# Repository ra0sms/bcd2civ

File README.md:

## Converter Yaesu BCD to Icom CI-V band data

A simple board is based on risk-v MCU CH32V003F4P6. 

* Dimensions: 70*45 mm
* Consumption current: 20 mA
* Power supply: from 7 to 20VDC
* CI-V address: 0x7A
* Baud rate for EW3MM tuner: 9600 kb/s
* Baud rate for DJ0ABR controller: 4800 kb/s

[Firmware for EU3MM tuner](code/obj/bcd2civ_tuner.hex)

[Firmware for DJ0ABR controller](code/obj/bcd2civ_dj0abr.hex)

More information - https://ra0sms.com/bcd2civ

### Yaesu BCD band data:

### Schematic:

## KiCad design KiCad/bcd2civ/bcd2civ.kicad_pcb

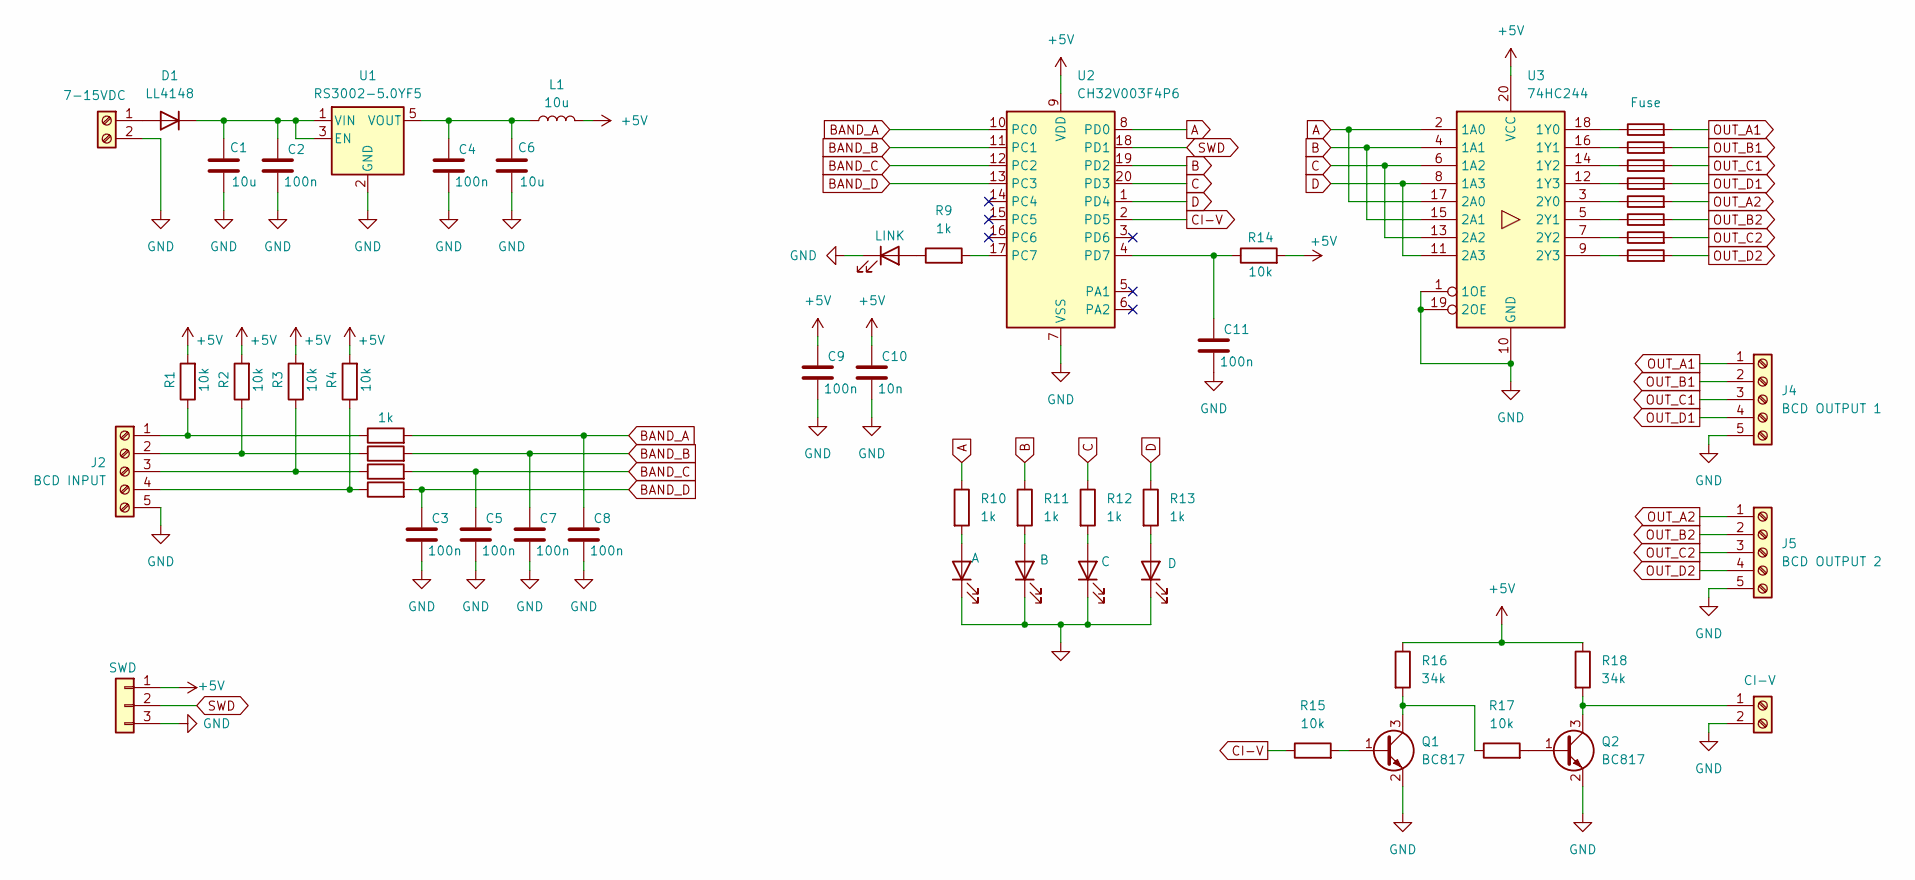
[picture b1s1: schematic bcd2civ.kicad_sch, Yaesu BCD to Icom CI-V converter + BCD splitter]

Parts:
C1, C6: 10u; C_1206_3216Metric_Pad1.33x1.80mm_HandSolder
C2, C3, C4, C5, C7, C8, C9, C11: 100n; C_1206_3216Metric_Pad1.33x1.80mm_HandSolder
C10: 10n; C_1206_3216Metric_Pad1.33x1.80mm_HandSolder
D1: LL4148; D_MiniMELF
D2: LINK; LED_1206_3216Metric
D3: A; LED_1206_3216Metric
D4: B; LED_1206_3216Metric
D5: C; LED_1206_3216Metric
D6: D; LED_1206_3216Metric
F1, F2, F3, F4, F5, F6, F7, F8: Fuse; R_1206_3216Metric
J1: 7-15VDC; TerminalBlock_MetzConnect_Type055_RT01502HDWU_1x02_P5.00mm_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
J2: BCD INPUT; TerminalBlock_MetzConnect_Type011_RT05505HBWC_1x05_P5.00mm_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
J3: SWD; PinSocket_1x03_P2.54mm_Vertical
J4: BCD OUTPUT 1; TerminalBlock_MetzConnect_Type011_RT05505HBWC_1x05_P5.00mm_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
J5: BCD OUTPUT 2; TerminalBlock_MetzConnect_Type011_RT05505HBWC_1x05_P5.00mm_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
J6: CI-V; TerminalBlock_MetzConnect_Type055_RT01502HDWU_1x02_P5.00mm_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
L1: 10u; L_1206_3216Metric
Q1, Q2: BC817; SOT-23
R1, R2, R3, R4, R14, R15, R17: 10k; R_1206_3216Metric
R5, R6, R7, R8, R9, R10, R11, R12, R13: 1k; R_1206_3216Metric
R16, R18: 34k; R_1206_3216Metric
U1: RS3002-5.0YF5; SOT-23-5
U2: CH32V003F4P6; TSSOP-20_4.4x6.5mm_P0.65mm
U3: 74HC244; TSSOP-20_4.4x6.5mm_P0.65mm

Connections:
+5V: C9.1, C10.1, J3.1, L1.2, R1.2, R2.2, R3.2, R4.2, R14.2, R16.1, R18.1, U2.9 (VDD), U3.20 (VCC)
A: R10.1, U2.8 (PD0), U3.2 (1A0), U3.17 (2A0)
B: R11.1, U2.19 (PD2), U3.4 (1A1), U3.15 (2A1)
BAND_A: C8.1, R5.2, U2.10 (PC0)
BAND_B: C7.1, R6.2, U2.11 (PC1)
BAND_C: C5.1, R7.2, U2.12 (PC2)
BAND_D: C3.1, R8.2, U2.13 (PC3)
C: R12.1, U2.20 (PD3), U3.6 (1A2), U3.13 (2A2)
CI-V: R15.1, U2.2 (PD5)
D: R13.1, U2.1 (PD4), U3.8 (1A3), U3.11 (2A3)
GND: C1.2, C2.2, C3.2, C4.2, C5.2, C6.2, C7.2, C8.2, C9.2, C10.2, C11.2, D2.1 (K), D3.1 (K), D4.1 (K), D5.1 (K), D6.1 (K), J1.2, J2.5, J3.3, J4.5, J5.5, J6.2, Q1.2 (E), Q2.2 (E), U1.2 (GND), U2.7 (VSS), U3.1 (1OE), U3.10 (GND), U3.19 (2OE)
unnamed: D1.2 (A), J1.1
unnamed: C1.1, C2.1, D1.1 (K), U1.1 (VIN), U1.3 (EN)
unnamed: D2.2 (A), R9.1
unnamed: D3.2 (A), R10.2
unnamed: D4.2 (A), R11.2
unnamed: D5.2 (A), R12.2
unnamed: D6.2 (A), R13.2
unnamed: J2.1, R1.1, R5.1
unnamed: J2.2, R2.1, R6.1
unnamed: J2.3, R3.1, R7.1
unnamed: J2.4, R4.1, R8.1
unnamed: J6.1, Q2.3 (C), R18.2
unnamed: Q1.1 (B), R15.2
unnamed: Q1.3 (C), R16.2, R17.1
unnamed: Q2.1 (B), R17.2
unnamed: C4.1, C6.1, L1.1, U1.5 (VOUT)
unnamed: R9.2, U2.17 (PC7)
unnamed: C11.1, R14.1, U2.4 (PD7)
unnamed: F1.1, U3.18 (1Y0)
unnamed: F2.1, U3.16 (1Y1)
unnamed: F3.1, U3.14 (1Y2)
unnamed: F4.1, U3.12 (1Y3)
unnamed: F5.1, U3.3 (2Y0)
unnamed: F6.1, U3.5 (2Y1)
unnamed: F7.1, U3.7 (2Y2)
unnamed: F8.1, U3.9 (2Y3)
OUT_A1: F1.2, J4.1
OUT_A2: F5.2, J5.1
OUT_B1: F2.2, J4.2
OUT_B2: F6.2, J5.2
OUT_C1: F3.2, J4.3
OUT_C2: F7.2, J5.3
OUT_D1: F4.2, J4.4
OUT_D2: F8.2, J5.4
SWD: J3.2, U2.18 (PD1)

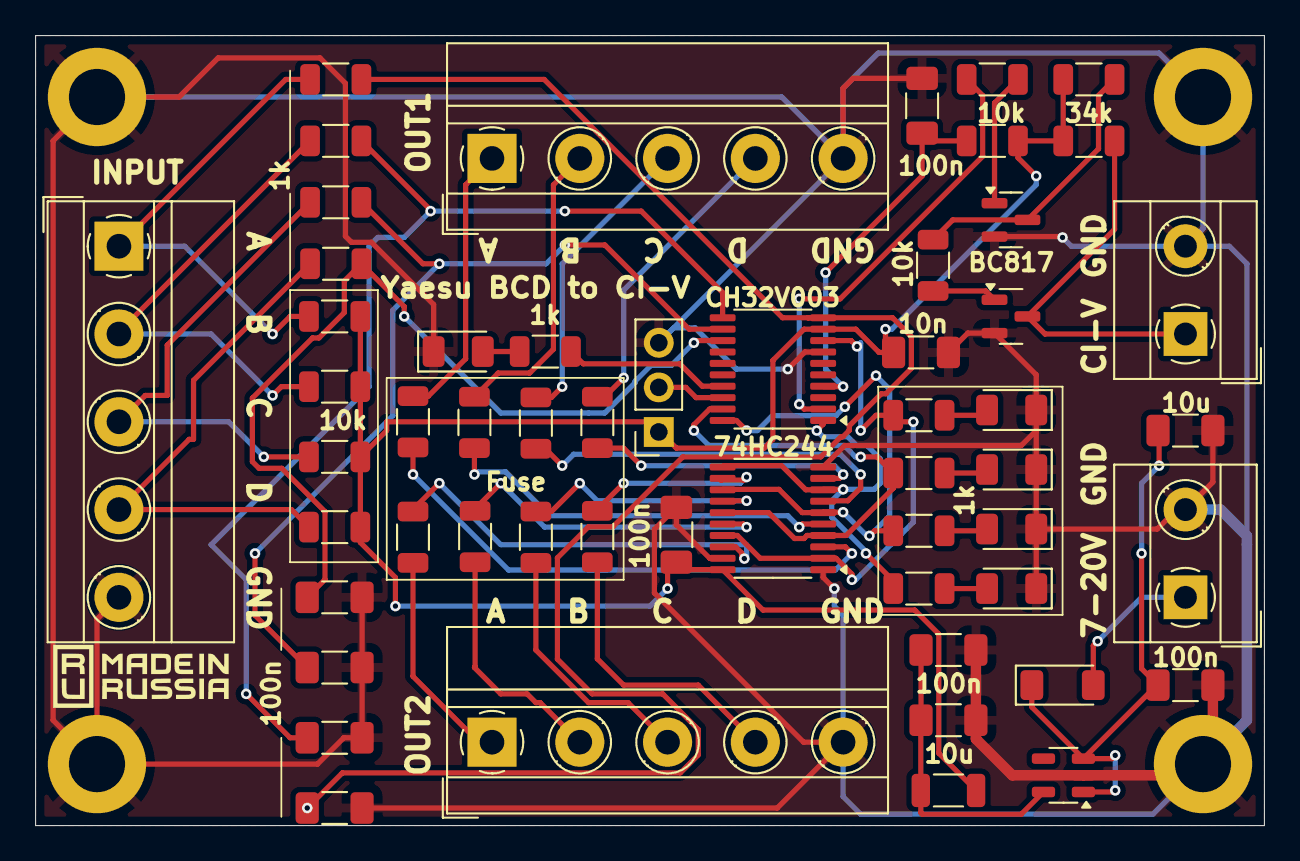
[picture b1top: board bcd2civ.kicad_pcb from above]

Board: 2 copper layers, 70.0 x 45.0 mm, 55 parts (0 on the bottom side), 46 nets.

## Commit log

2024-10-01 first
2024-10-02 add pics
2025-03-19 some fixes
2025-07-14 fix ci-v interrupt issue
2025-08-07 add firmware for tuiner ew3mm
2025-08-08 fix some issues
